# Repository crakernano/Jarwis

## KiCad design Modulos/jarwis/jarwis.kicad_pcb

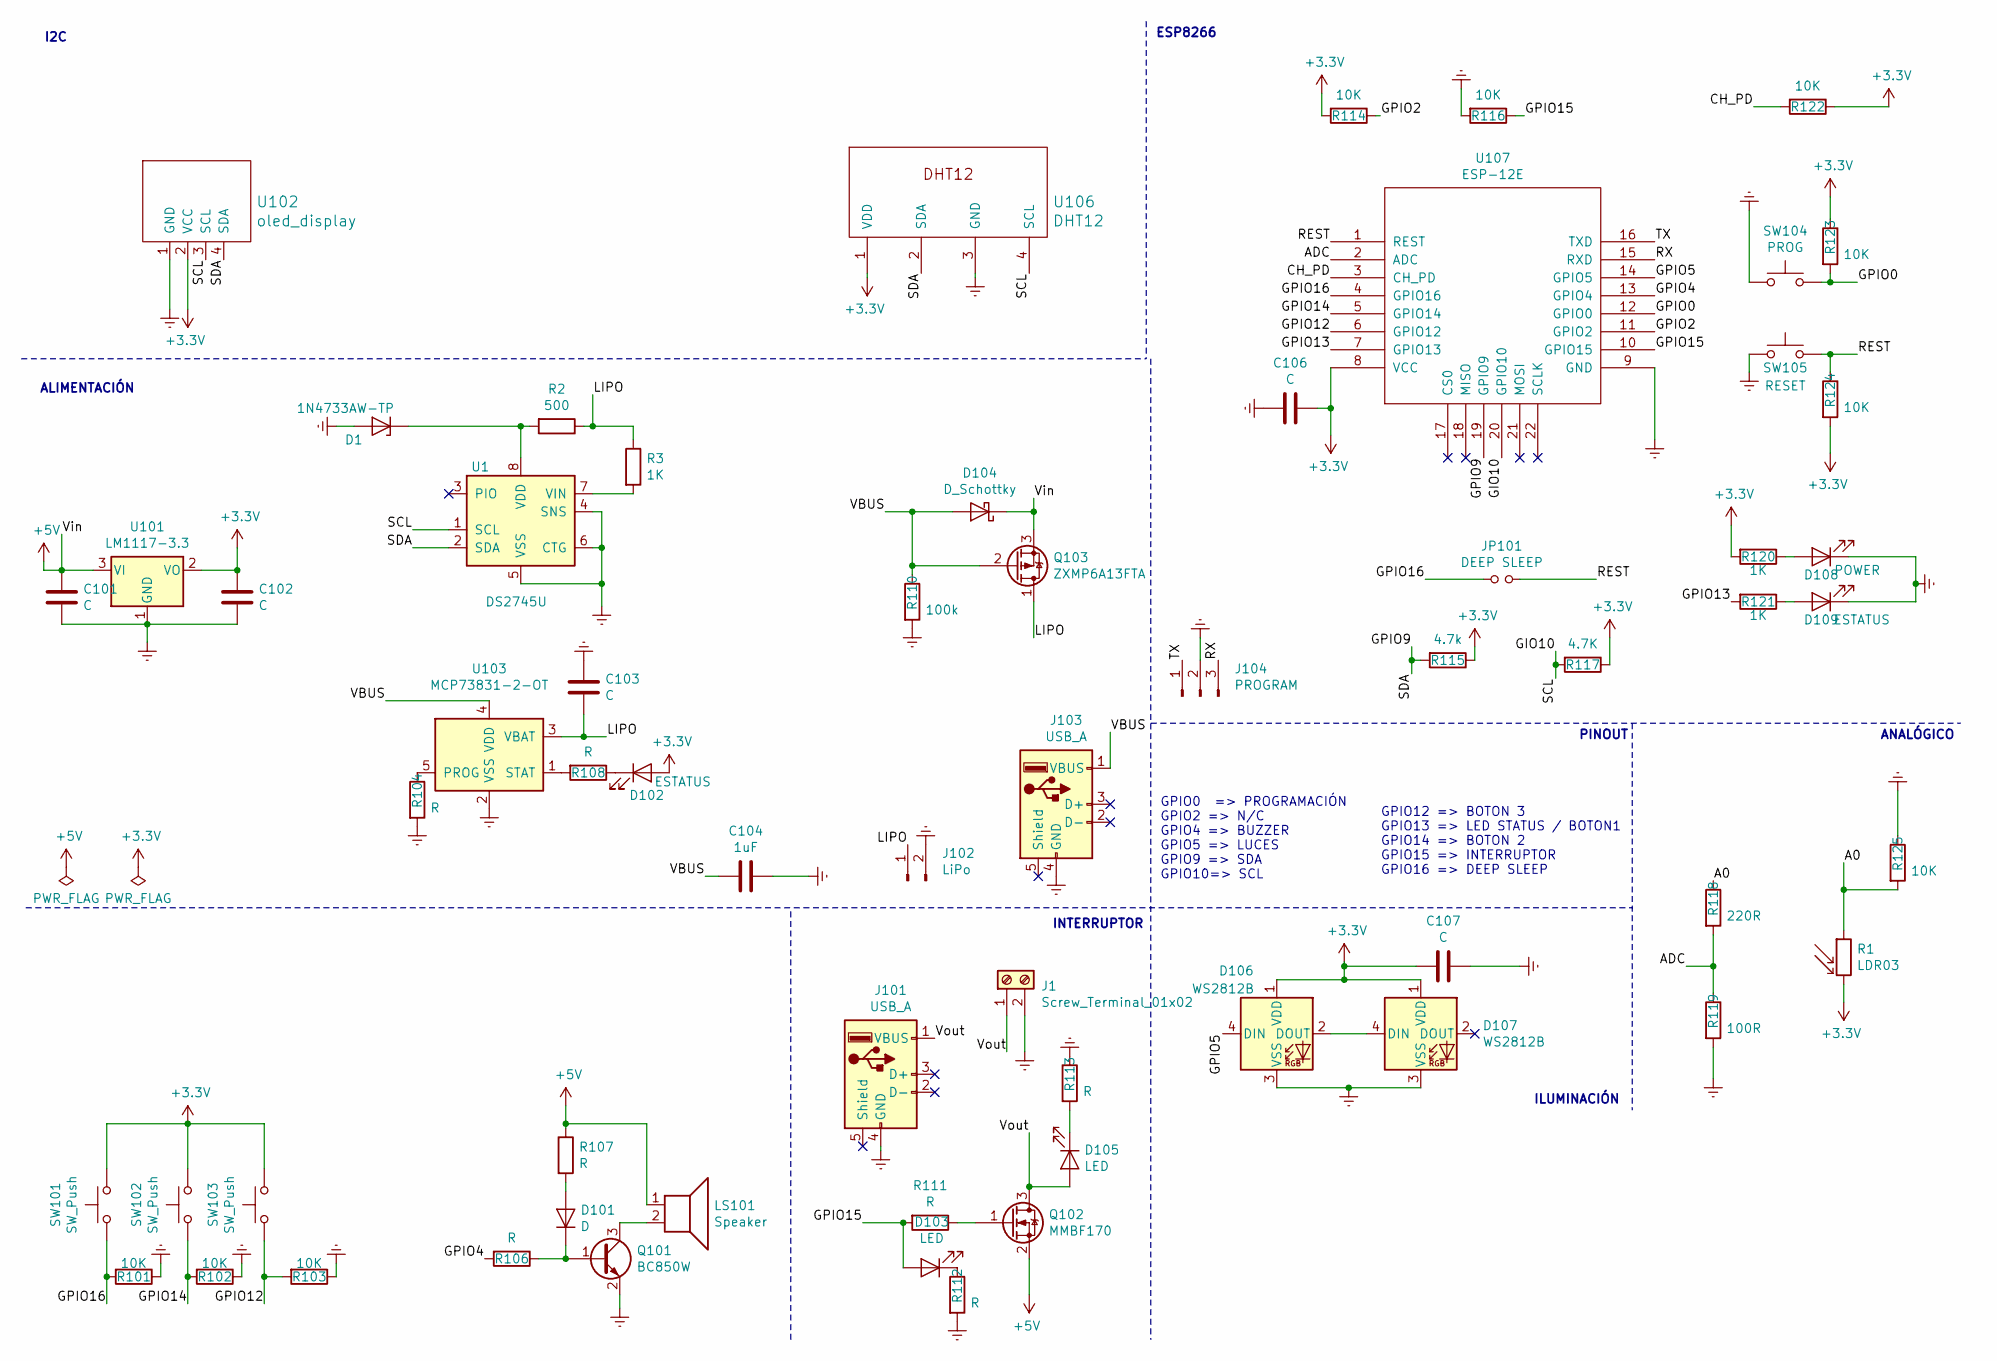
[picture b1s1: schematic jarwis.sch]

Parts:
C101, C102, C103, C106, C107: C; C_0805_2012Metric_Pad1.15x1.40mm_HandSolder
C104: 1uF; C_0805_2012Metric_Pad1.15x1.40mm_HandSolder
D1: 1N4733AW-TP; D_0805_2012Metric_Pad1.15x1.40mm_HandSolder
D101: D; D_0805_2012Metric_Pad1.15x1.40mm_HandSolder
D102, D109: ESTATUS; LED_0805_2012Metric_Pad1.15x1.40mm_HandSolder
D103, D105: LED; LED_0805_2012Metric_Pad1.15x1.40mm_HandSolder
D104: D_Schottky; D_0805_2012Metric_Pad1.15x1.40mm_HandSolder
D106, D107: WS2812B; LED_WS2812B_PLCC4_5.0x5.0mm_P3.2mm
D108: POWER; LED_0805_2012Metric_Pad1.15x1.40mm_HandSolder
J1: Screw_Terminal_01x02; TerminalBlock_bornier-2_P5.08mm
J101: USB_A; FCI_87520-0010BLF
J102: LiPo; PinHeader_1x02_P2.54mm_Vertical
J103: USB_A; USB_Micro-B_Wuerth_629105150521_CircularHoles
J104: PROGRAM; PinHeader_1x03_P2.54mm_Vertical
JP101: DEEP SLEEP; SolderJumper-2_P1.3mm_Open_RoundedPad1.0x1.5mm
LS101: Speaker; MagneticBuzzer_Kingstate_KCG0601
Q101: BC850W; SOT-323_SC-70
Q102: MMBF170; SOT-23
Q103: ZXMP6A13FTA; SOT-23_Handsoldering
R1: LDR03; R_LDR_7x6mm_P5.1mm_Vertical
R2: 500; R_0805_2012Metric_Pad1.15x1.40mm_HandSolder
R3, R120, R121: 1K; R_0805_2012Metric_Pad1.15x1.40mm_HandSolder
R101, R102, R103, R114, R116, R122, R123, R124, R125: 10K; R_0805_2012Metric_Pad1.15x1.40mm_HandSolder
R104, R106, R107, R108, R111, R112, R113: R; R_0805_2012Metric_Pad1.15x1.40mm_HandSolder
R110: 100k; R_0805_2012Metric_Pad1.15x1.40mm_HandSolder
R115: 4.7k; R_0805_2012Metric_Pad1.15x1.40mm_HandSolder
R117: 4.7K; R_0805_2012Metric_Pad1.15x1.40mm_HandSolder
R118: 220R; R_0805_2012Metric_Pad1.15x1.40mm_HandSolder
R119: 100R; R_0805_2012Metric_Pad1.15x1.40mm_HandSolder
SW101, SW102, SW103: SW_Push; SW_SPST_B3S-1000
SW104: PROG; SW_Tactile_SPST_Angled_PTS645Vx31-2LFS
SW105: RESET; SW_Tactile_SPST_Angled_PTS645Vx31-2LFS
U1: DS2745U; TSSOP-8_3x3mm_P0.65mm
U101: LM1117-3.3; SOT-223-3_TabPin2
U102: oled_display; oled_display_0.96
U103: MCP73831-2-OT; SOT-23-5
U106: DHT12
U107: ESP-12E; ESP-12E_SMD

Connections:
+3V3: C102.1, C106.1, C107.2, D102.2 (A), D106.1 (VDD), D107.1 (VDD), R1.2, R114.2, R115.1, R117.1, R120.2, R122.1, R123.1, R124.2, SW101.2, SW102.2, SW103.2, U101.2 (VO), U102.2 (VCC), U106.1 (VDD), U107.8 (VCC)
+5V: C101.1, D104.1 (K), LS101.1, Q102.2 (S), Q103.3 (S), R107.1, U101.3 (VI)
/A0: R1.1, R118.1, R125.2
/ADC: R118.2, R119.1, U107.2 (ADC)
/CH_PD: R122.2, U107.3 (CH_PD)
/GIO10: R117.2, U1.1 (SCL), U102.3 (SCL), U106.4 (SCL), U107.20 (GPIO10)
/GPIO0: R123.2, SW104.2, U107.12 (GPIO0)
/GPIO2: R114.1, U107.11 (GPIO2)
/GPIO4: R106.2, U107.13 (GPIO4)
/GPIO5: D106.4 (DIN), U107.14 (GPIO5)
/GPIO9: R115.2, U1.2 (SDA), U102.4 (SDA), U106.2 (SDA), U107.19 (GPIO9)
/GPIO12: R103.2, SW103.1, U107.6 (GPIO12)
/GPIO13: R121.2, U107.7 (GPIO13)
/GPIO14: R102.2, SW102.1, U107.5 (GPIO14)
/GPIO15: D103.2 (A), R111.2, R116.1, U107.10 (GPIO15)
/GPIO16: JP101.1, R101.2, SW101.1, U107.4 (GPIO16)
/LIPO: C103.2, J102.1, Q103.1 (D), R2.1, R3.1, U103.3 (VBAT)
/REST: JP101.2, R124.1, SW105.2, U107.1 (REST)
/RX: J104.3, U107.15 (RXD)
/TX: J104.1, U107.16 (TXD)
/VBUS: C104.2, D104.2 (A), J103.1 (VBUS), Q103.2 (G), R110.1, U103.4 (VDD)
/Vout: D105.2 (A), J1.1, J101.1 (VBUS), Q102.3 (D)
Earth: C101.2, C102.2, C103.1, C104.1, C106.2, C107.1, D1.2 (A), D106.3 (VSS), D107.3 (VSS), D108.1 (K), D109.1 (K), J1.2, J101.4 (GND), J102.2, J103.4 (GND), J104.2, Q101.2 (E), R101.1, R102.1, R103.1, R104.2, R110.2, R112.2, R113.1, R116.2, R119.2, R125.1, SW104.1, SW105.1, U1.4 (SNS), U1.5 (VSS), U1.6 (CTG), U101.1 (GND), U102.1 (GND), U103.2 (VSS), U106.3 (GND), U107.9 (GND)
unnamed: D1.1 (K), R2.2, U1.8 (VDD)
unnamed: D101.1 (K), Q101.1 (B), R106.1
unnamed: D101.2 (A), R107.2
unnamed: D102.1 (K), R108.1
unnamed: D103.1 (K), R112.1
unnamed: D105.1 (K), R113.2
unnamed: D106.2 (DOUT), D107.4 (DIN)
unnamed: D108.2 (A), R120.1
unnamed: D109.2 (A), R121.1
unnamed: LS101.2, Q101.3 (C)
unnamed: Q102.1 (G), R111.1
unnamed: R3.2, U1.7 (VIN)
unnamed: R104.1, U103.5 (PROG)
unnamed: R108.2, U103.1 (STAT)

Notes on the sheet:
PINOUT
GPIO0 => PROGRAMACIÓN GPIO2 => N/C GPIO4 => BUZZER GPIO5 => LUCES GPIO9 => SDA GPIO10=> SCL
GPIO12 => BOTON 3 GPIO13 => LED STATUS / BOTON1 GPIO14 => BOTON 2 GPIO15 => INTERRUPTOR GPIO16 => DEEP SLEEP
I2C
ALIMENTACIÓN
ESP8266
ANALÓGICO
INTERRUPTOR
ILUMINACIÓN

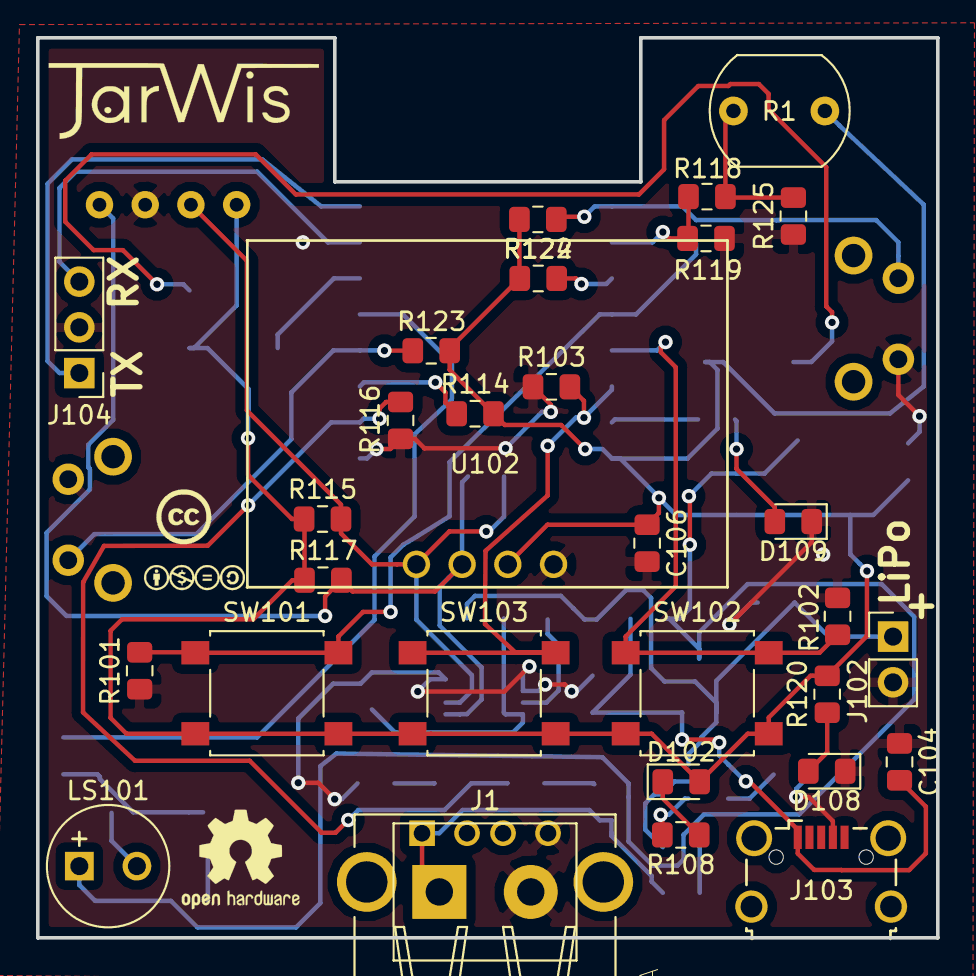
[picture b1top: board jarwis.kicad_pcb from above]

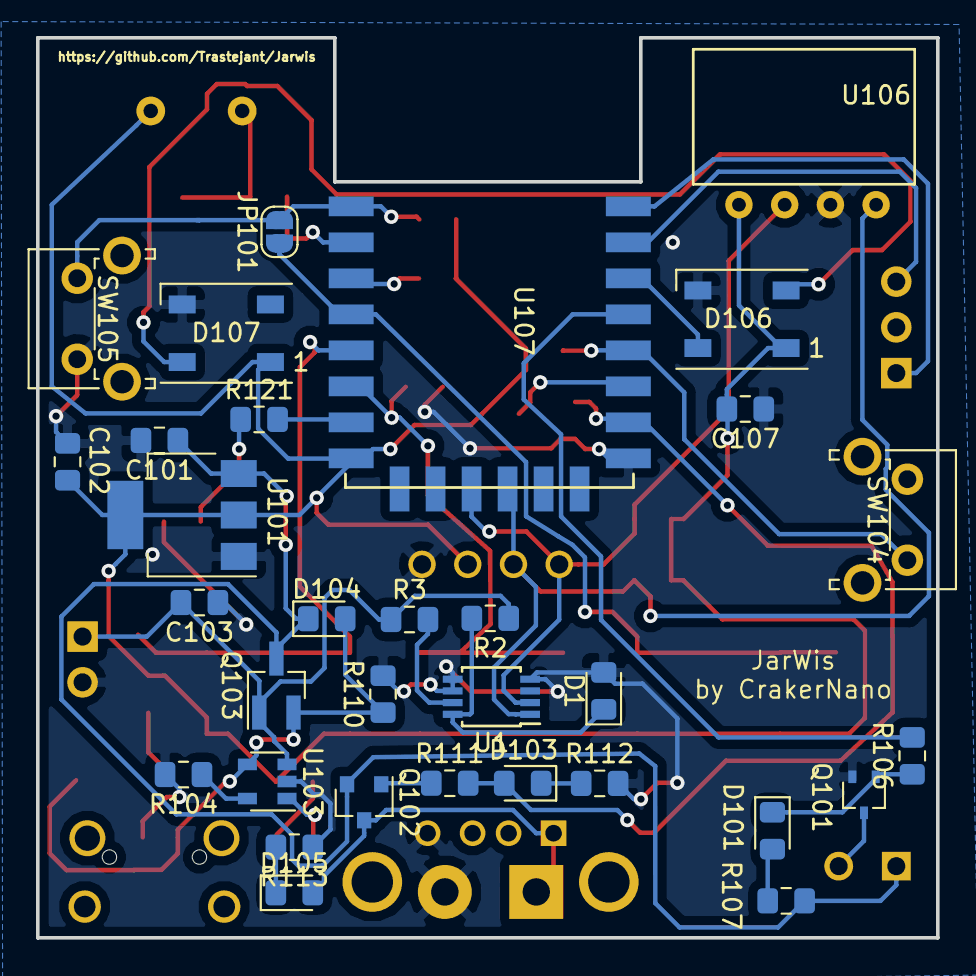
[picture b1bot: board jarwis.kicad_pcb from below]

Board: 2 copper layers, 50.0 x 50.0 mm, 63 parts (32 on the bottom side), 37 nets.

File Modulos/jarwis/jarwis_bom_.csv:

Component,Description,Part,References,Value,Footprint,Quantity Per PCB,Datasheet
1,Unpolarized capacitor,C,C104,1uF,C_0805_2012Metric_Pad1.15x1.40mm_HandSolder,1,~
2,Unpolarized capacitor,C,C101 C102 C103 C106 C107,C,C_0805_2012Metric_Pad1.15x1.40mm_HandSolder,5,~
3,"1300mW Silicon planar power Zener diodes, DO-41",1N47xxA,D1,1N4733AW-TP,D_0805_2012Metric_Pad1.15x1.40mm_HandSolder,1,https://www.vishay.com/docs/85816/1n4728a.pdf
4,Diode,D,D101,D,D_0805_2012Metric_Pad1.15x1.40mm_HandSolder,1,~
5,Schottky diode,D_Schottky,D104,D_Schottky,D_0805_2012Metric_Pad1.15x1.40mm_HandSolder,1,~
6,LED generic,LED,D102 D109,ESTATUS,LED_0805_2012Metric_Pad1.15x1.40mm_HandSolder,2,~
7,LED generic,LED,D103 D105,LED,LED_0805_2012Metric_Pad1.15x1.40mm_HandSolder,2,~
8,LED generic,LED,D108,POWER,LED_0805_2012Metric_Pad1.15x1.40mm_HandSolder,1,~
9,RGB LED with integrated controller,WS2812B,D106 D107,WS2812B,LED_WS2812B_PLCC4_5.0x5.0mm_P3.2mm,2,https://cdn-shop.adafruit.com/datasheets/WS2812B.pdf
10,"Generic connector, single row, 01x02, script generated (kicad-library-utils/schlib/autogen/connector/)",Conn_01x02_Male,J102,LiPo,PinHeader_1x02_P2.54mm_Vertical,1,~
11,"Generic connector, single row, 01x03, script generated (kicad-library-utils/schlib/autogen/connector/)",Conn_01x03_Male,J104,PROGRAM,PinHeader_1x03_P2.54mm_Vertical,1,~
12,"Generic screw terminal, single row, 01x02, script generated (kicad-library-utils/schlib/autogen/connector/)",Screw_Terminal_01x02,J1,Screw_Terminal_01x02,TerminalBlock_bornier-2_P5.08mm,1,~
13,USB Type A connector,USB_A,J101,USB_A,FCI_87520-0010BLF,1, ~
14,USB Type A connector,USB_A,J103,USB_A,USB_Micro-B_Wuerth_629105150521_CircularHoles,1, ~
15,"Jumper, normally open",Jumper_NO_Small,JP101,DEEP SLEEP,SolderJumper-2_P1.3mm_Open_RoundedPad1.0x1.5mm,1,~
16,speaker,Speaker,LS101,Speaker,MagneticBuzzer_Kingstate_KCG0601,1,~
17,"0.1A Ic, 45V Vce, NPN Transistor, SOT-323",BC850W,Q101,BC850W,SOT-323_SC-70,1,http://www.infineon.com/dgdl/Infineon-BC847SERIES_BC848SERIE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
18,"60V Vds, 0.5 A Id, N-channel MOSFET, SOT-23",MMBF170,Q102,MMBF170,SOT-23,1,https://www.diodes.com/assets/Datasheets/ds30104.pdf
19,Transistor P-MOSFET with substrate diode (general),Q_PMOS_DGS,Q103,ZXMP6A13FTA,SOT-23_Handsoldering,1,~
20,Resistor,R,R119,100R,R_0805_2012Metric_Pad1.15x1.40mm_HandSolder,1,~
21,Resistor,R,R110,100k,R_0805_2012Metric_Pad1.15x1.40mm_HandSolder,1,~
22,Resistor,R,R101 R102 R103 R114 R116 R122 R123 R124 R125,10K,R_0805_2012Metric_Pad1.15x1.40mm_HandSolder,9,~
23,Resistor,R,R3 R120 R121,1K,R_0805_2012Metric_Pad1.15x1.40mm_HandSolder,3,~
24,Resistor,R,R118,220R,R_0805_2012Metric_Pad1.15x1.40mm_HandSolder,1,~
25,Resistor,R,R115 R117,4.7k,R_0805_2012Metric_Pad1.15x1.40mm_HandSolder,2,~
26,Resistor,R,R2,500,R_0805_2012Metric_Pad1.15x1.40mm_HandSolder,1,~
27,light dependent resistor,LDR03,R1,LDR03,R_LDR_7x6mm_P5.1mm_Vertical,1,http://www.elektronica-componenten.nl/WebRoot/StoreNL/Shops/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
28,Resistor,R,R104 R106 R107 R108 R111 R112 R113,R,R_0805_2012Metric_Pad1.15x1.40mm_HandSolder,7,~
29,"Push button switch, generic, two pins",SW_Push,SW104,PROG,SW_Tactile_SPST_Angled_PTS645Vx31-2LFS,1,
30,"Push button switch, generic, two pins",SW_Push,SW105,RESET,SW_Tactile_SPST_Angled_PTS645Vx31-2LFS,1,
31,"Push button switch, generic, two pins",SW_Push,SW101 SW102 SW103,SW_Push,SW_SPST_B3S-1000,3,
32,,DHT12,U106,DHT12,DHT12,1,
33,"Current-flow, voltage and temperature  measurement to support batterycapacity monitoring, 2.5V to 4.5V VDD, -40 to +85 degree Celcius, TSSOP-8",DS2745U,U1,DS2745U,TSSOP-8_3x3mm_P0.65mm,1,https://datasheets.maximintegrated.com/en/ds/DS2745.pdf
34,"ESP8266 ESP-12E module, 22 pins, 2mm, PCB antenna",ESP-12E,U107,ESP-12E,ESP-12E_SMD,1,http://l0l.org.uk/2014/12/esp8266-modules-hardware-guide-got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
35,"800mA Low-Dropout Linear Regulator, 3.3V fixed output, TO-220/TO-252/TO-263/SOT-223",LM1117-3.3,U101,LM1117-3.3,SOT-223-3_TabPin2,1,http://www.ti.com/lit/ds/symlink/lm1117.pdf
36,"Single cell, Li-Ion/Li-Po charge management controller, 4.20V, Tri-State Status Output, in SOT23-5 package",MCP73831-2-OT,U103,MCP73831-2-OT,SOT-23-5,1,http://ww1.microchip.com/downloads/en/DeviceDoc/20001984g.pdf
37,,oled_display,U102,oled_display,oled_display_0.96,1,





Component Groups:,37
Component Count:,63
Fitted Components:,63
Number of PCBs:,1
Total components:,63
Schematic Version:,
Schematic Date:,
BoM Date:,sb 27 abr 2019 20:41:01 CEST
Schematic Source:,/home/nano/Desarrollos/git/jarwis/Hardware/jarwis/jarwis.sch
KiCad Version:,Eeschema 5.0.2-bee76a0~70~ubuntu18.04.1

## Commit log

2019-01-16 Push inicial
2019-01-25 Firmware de la estación meteorolica externa de Jarwis
2019-01-28 Añadido el Firmware para el Attiny de los modulos JGG
    Esta versión es capaz de emitir por 433Mhz las lecturas de humedad del suelo y luminosidad
    Working progress:
    La librería para leer el sensor de humedad ambiental y temperatura por i2c no funciona correctamente
    Falta la comunicación I2C entre el Attiny85 y el ESP8266
2019-04-27 PCB del modulo principal de Jarwis (En pruebas)
2019-04-27 Imagenes de la PCB
2019-06-23 Librerias Python para el servidor
2019-07-07 Pendiente de limpieza
2019-07-16 Server core
